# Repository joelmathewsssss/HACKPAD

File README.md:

# The Player 
This is my highway hackpad! It's used for controlling my spotify using a song backwards, pause/play, forwards and go next and previous page. It has a rotary encoder for changing the volume. and I displays a legend on the OLED. I did this project as it was a starter project and my first Hardware YSWS. Never got to finish it till now, after I've gotten more experience with hardware.

# Schematic and PCB

# CAD

# Built

# Components
- 5x Cherry MX Switches
- 1x SK6812 MINI Leds
- 1x XIAO RP2040
- 5x Keycaps
- 1x EC11 Rotary Encoder
- 1x .91" OLED Display
- Custom 3D Printed Top Case
- Custom 3D Printed Bottom Case

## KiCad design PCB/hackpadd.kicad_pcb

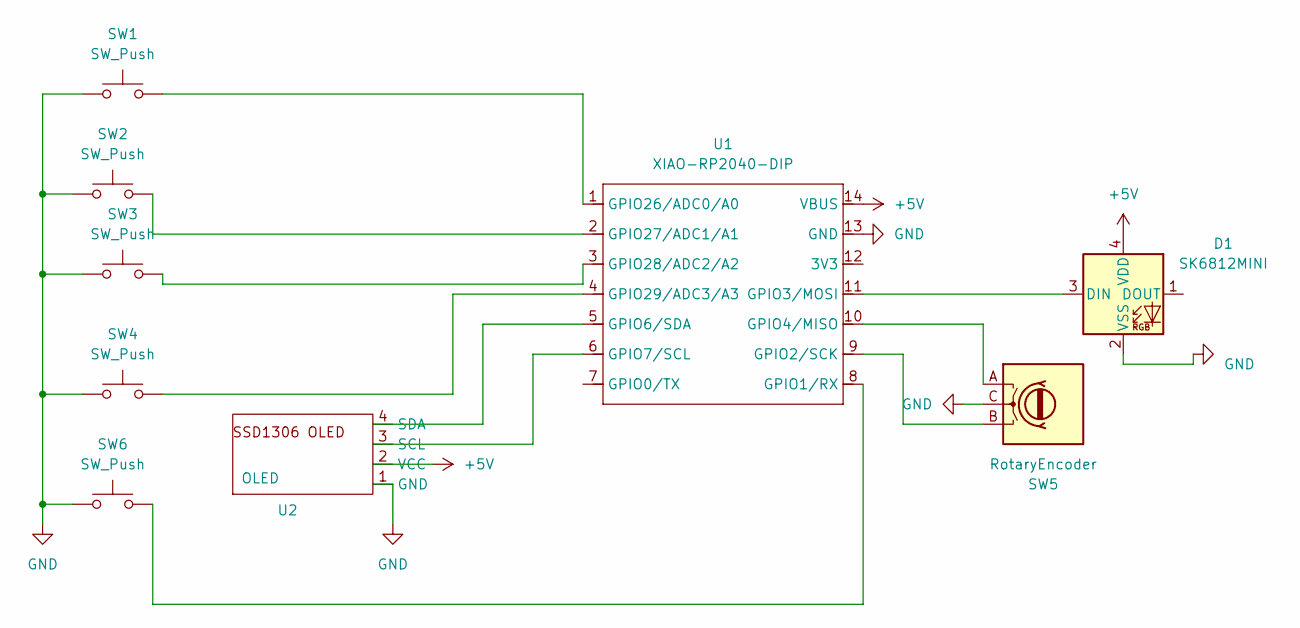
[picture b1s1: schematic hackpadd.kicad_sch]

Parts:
D1: SK6812MINI; LED_SK6812MINI_PLCC4_3.5x3.5mm_P1.75mm
SW1, SW2, SW3, SW4, SW6: SW_Push; SW_Cherry_MX_1.00u_PCB
SW5: RotaryEncoder; RotaryEncoder_Alps_EC11E_Vertical_H20mm
U1: XIAO-RP2040-DIP
U2: OLED; SSD1306-0.91-OLED-4pin-128x32 (1)

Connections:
+5V: D1.4 (VDD), U1.14 (VBUS), U2.2 (VCC)
GND: D1.2 (VSS), SW1.1, SW2.1, SW3.1, SW4.1, SW5.C, SW6.1, U1.13 (GND), U2.1 (GND)
unnamed: D1.3 (DIN), U1.11 (GPIO3/MOSI)
unnamed: SW6.2, U1.8 (GPIO1/RX)
unnamed: SW5.B, U1.9 (GPIO2/SCK)
unnamed: SW5.A, U1.10 (GPIO4/MISO)
unnamed: U1.5 (GPIO6/SDA), U2.4 (SDA)
unnamed: U1.6 (GPIO7/SCL), U2.3 (SCL)
unnamed: SW1.2, U1.1 (GPIO26/ADC0/A0)
unnamed: SW2.2, U1.2 (GPIO27/ADC1/A1)
unnamed: SW3.2, U1.3 (GPIO28/ADC2/A2)
unnamed: SW4.2, U1.4 (GPIO29/ADC3/A3)

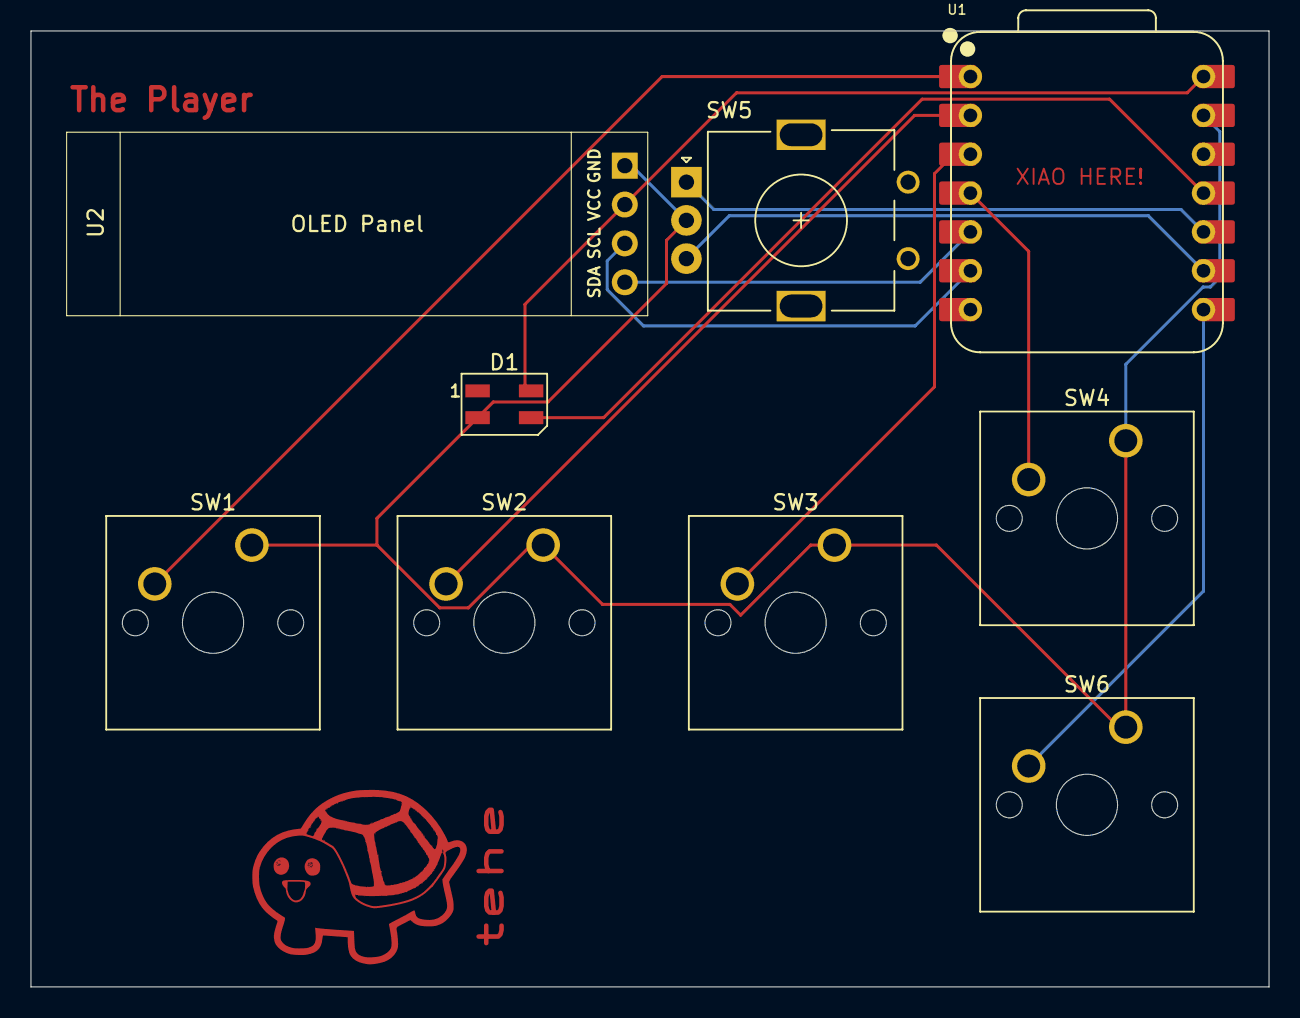
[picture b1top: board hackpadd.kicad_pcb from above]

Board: 2 copper layers, 81.0 x 62.5 mm, 9 parts (0 on the bottom side), 12 nets.

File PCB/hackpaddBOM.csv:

"Id";"Designator";"Footprint";"Quantity";"Designation";"Supplier and ref";
1;"U2";"SSD1306-0.91-OLED-4pin-128x32 (1)";1;"OLED";;;
2;"SW5";"RotaryEncoder_Alps_EC11E_Vertical_H20mm";1;"RotaryEncoder";;;
3;"SW4";"SW_Cherry_MX_1.00u_PCB";1;"SW_Push";;;
4;"D1";"LED_SK6812MINI_PLCC4_3.5x3.5mm_P1.75mm";1;"SK6812MINI";;;
5;"SW6,SW1,SW3,SW2";"SW_Cherry_MX_1.00u_PCB";4;"SW_Push";;;
6;"U1";"XIAO-RP2040-DIP";1;"XIAO-RP2040-DIP";;;

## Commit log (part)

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2025-06-11 Schem changes
2025-06-12 finish schem and pcb
2025-06-29 Sync files
2025-06-29 updt
